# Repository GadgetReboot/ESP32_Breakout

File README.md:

# ESP32_Breakout
ESP32 module breakout board
<br><br><br><br>

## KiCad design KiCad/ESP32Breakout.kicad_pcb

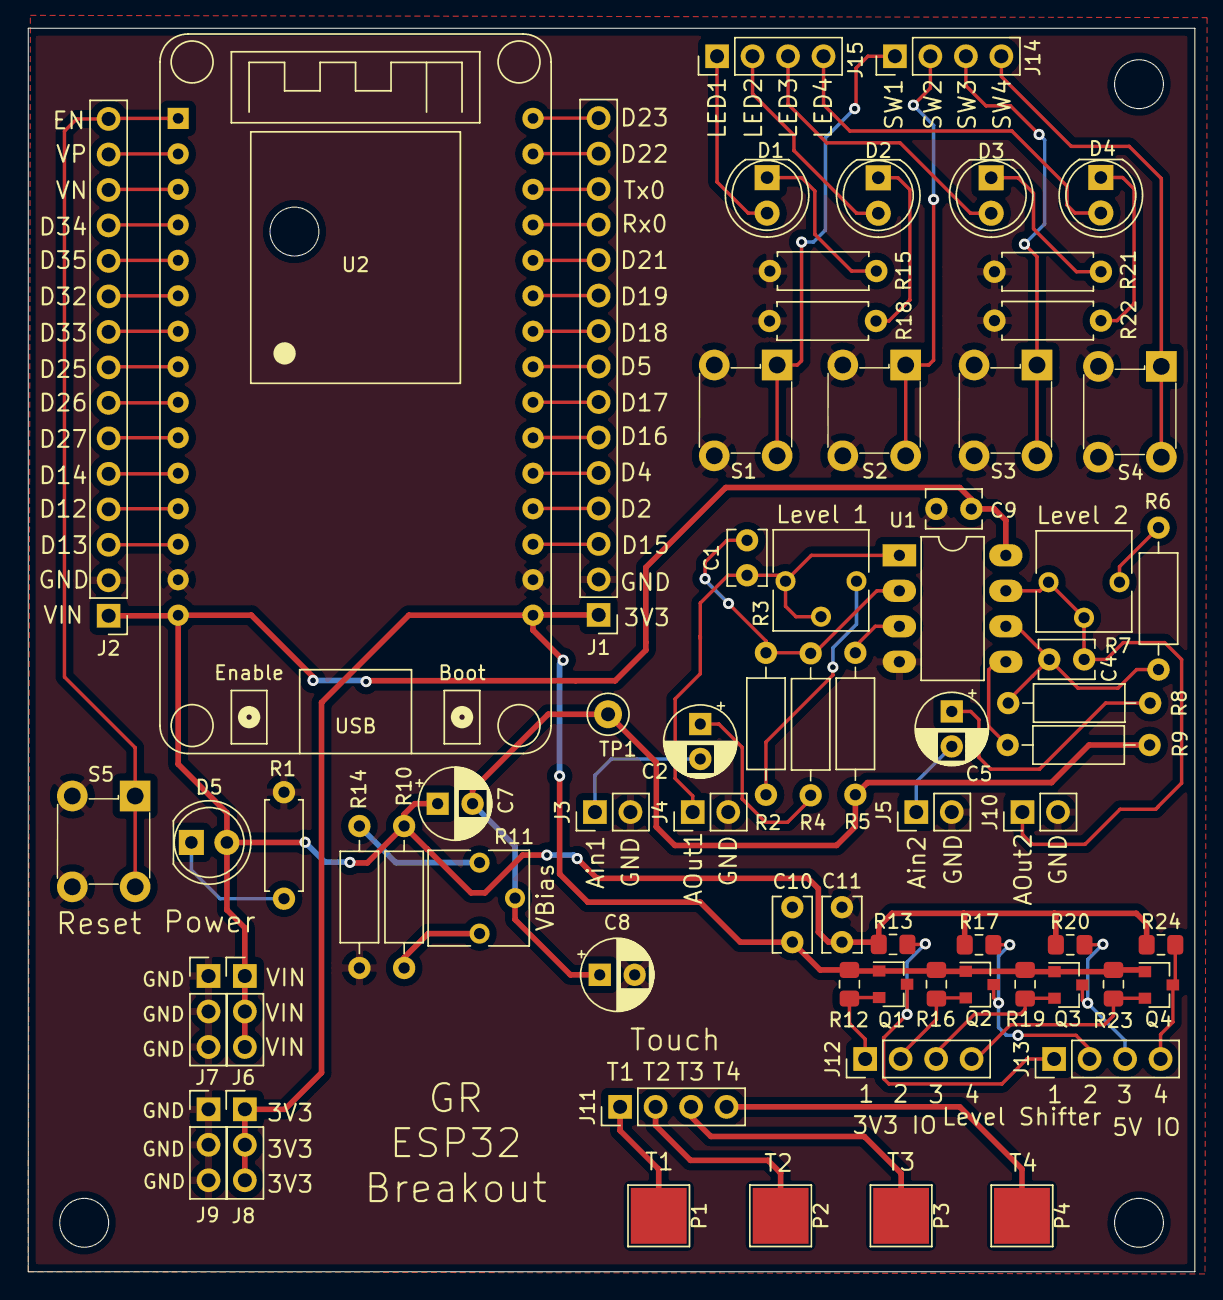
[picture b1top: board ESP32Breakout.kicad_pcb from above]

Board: 2 copper layers, 83.5 x 89.0 mm, 73 parts (0 on the bottom side), 69 nets.

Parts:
C1, C4: 100pF; C_Disc_D3.8mm_W2.6mm_P2.50mm
C2, C5: 10uF; CP_Radial_D5.0mm_P2.50mm
C7, C8: 47uF; CP_Radial_D5.0mm_P2.50mm
C9, C10, C11: 100nF; C_Disc_D3.8mm_W2.6mm_P2.50mm
D1, D2, D3, D4, D5: LED_Small_ALT; LED_D5.0mm_Clear
H1, H2, H3, H4: MountingHole; MountingHole_3.5mm
J1, J2: Conn_01x15; PinHeader_1x15_P2.54mm_Vertical
J3, J4, J5, J10: Conn_01x02; PinHeader_1x02_P2.54mm_Vertical
J6, J7, J8, J9: UART; PinHeader_1x03_P2.54mm_Vertical
J11, J12, J13, J14, J15: Conn_01x04; PinHeader_1x04_P2.54mm_Vertical
P1, P2, P3, P4: Conn_01x01; Touch_Pad_15x15mm
Q1, Q2, Q3, Q4: BSS138; SOT-23
R1: 300r; R_Axial_DIN0207_L6.3mm_D2.5mm_P7.62mm_Horizontal
R2, R5, R6, R9: 1K; R_Axial_DIN0207_L6.3mm_D2.5mm_P10.16mm_Horizontal
R3, R7, R11: 100K; Potentiometer_Vishay_T73YP_Vertical
R4, R8: 10K; R_Axial_DIN0207_L6.3mm_D2.5mm_P10.16mm_Horizontal
R10, R14: 47K; R_Axial_DIN0207_L6.3mm_D2.5mm_P10.16mm_Horizontal
R12, R13, R16, R17, R19, R20, R23, R24: 10K; R_0805_2012Metric_Pad1.15x1.40mm_HandSolder
R15, R18, R21, R22: 200r; R_Axial_DIN0207_L6.3mm_D2.5mm_P7.62mm_Horizontal
S1, S2, S3, S4, S5: 1825910-6; Switch_Tactile_THT_6x6mm
TP1: TestPoint; TestPoint_Loop_D1.80mm_Drill1.0mm_Beaded
U1: LM358; DIP-8_W7.62mm_LongPads
U2: ESP32_DevKit_V1_DOIT; esp32_devkit_v1_doit

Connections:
/3V3: C10.1, J1.1, J8.1, J8.2, J8.3, Q1.1, Q2.1, Q3.1, Q4.1, R12.1, R16.1, R19.1, R23.1, U2.16
/D2: J1.4, U2.19
/D4: J1.5, U2.20
/D5: J1.8, U2.23
/D12: J2.4, U2.12
/D13: J2.3, U2.13
/D14: J2.5, U2.11
/D15: J1.3, U2.18
/D16: J1.6, U2.21
/D17: J1.7, U2.22
/D18: J1.9, U2.24
/D19: J1.10, U2.25
/D21: J1.11, U2.26
/D22: J1.14, U2.29
/D23: J1.15, U2.30
/D25: J2.8, U2.8
/D26: J2.7, U2.9
/D27: J2.6, U2.10
/D32: J2.10, U2.6
/D33: J2.9, U2.7
/D34: J2.12, U2.4
/D35: J2.11, U2.5
/EN: J2.15, S5.1, S5.2, U2.1
/Rx0: J1.12, U2.27
/Tx0: J1.13, U2.28
/VIN: C7.1, C9.1, C11.2, D5.2, J2.1, J6.1, J6.2, J6.3, R10.1, R13.1, R17.1, R20.1, R24.1, U1.8, U2.15
/VN: J2.13, U2.3
/VP: J2.14, U2.2
GND: C8.2, C9.2, C11.1, J1.2, J2.2, J3.2, J4.2, J5.2, J7.1, J7.2, J7.3, J9.1, J9.2, J9.3, J10.2, R1.2, R14.2, R15.2, R18.2, R21.2, R22.2, S1.3, S1.4, S2.3, S2.4, S3.3, S3.4, S4.3, S4.4, S5.3, S5.4, U1.4, U2.14, U2.17
GNDA: C7.2, C8.1, R5.2, R9.2, R11.2, TP1.1
unnamed: C1.1, J4.1, R3.1, R3.2, U1.1
unnamed: C1.2, R2.1, R4.2, U1.2
unnamed: C2.1, R4.1
unnamed: C2.2, J3.1
unnamed: C4.1, J10.1, R7.1, R7.2, U1.7
unnamed: C4.2, R6.1, R8.2, U1.6
unnamed: C5.1, R8.1
unnamed: C5.2, J5.1
unnamed: D1.1, R15.1
unnamed: D1.2, J15.1
unnamed: D2.1, R18.1
unnamed: D2.2, J15.2
unnamed: D3.1, R21.1
unnamed: D3.2, J15.3
unnamed: D4.1, R22.1
unnamed: D4.2, J15.4
unnamed: D5.1, R1.1
unnamed: J11.1, P1.1
unnamed: J11.2, P2.1
unnamed: J11.3, P3.1
unnamed: J11.4, P4.1
unnamed: J12.1, Q1.2, R12.2
unnamed: J12.2, Q2.2, R16.2
unnamed: J12.3, Q3.2, R19.2
unnamed: J12.4, Q4.2, R23.2
unnamed: J13.1, Q1.3, R13.2
unnamed: J13.2, Q2.3, R17.2
unnamed: J13.3, Q3.3, R20.2
unnamed: J13.4, Q4.3, R24.2
unnamed: J14.1, S1.1, S1.2
unnamed: J14.2, S2.1, S2.2
unnamed: J14.3, S3.1, S3.2
unnamed: J14.4, S4.1, S4.2
unnamed: R2.2, R3.3
unnamed: R5.1, U1.3
unnamed: R6.2, R7.3
unnamed: R9.1, U1.5
unnamed: R10.2, R11.1
unnamed: R11.3, R14.1
